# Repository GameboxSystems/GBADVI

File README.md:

# GBADVI

GBADVI is a custom DVI driver written in VHDL for the Gameboy Advance. It employs a custom PCB based around the Spartan-6 (XC6SLX9) FPGA that takes in GBA display and control signals (through SNES port), stores frames in SDRAM, and outputs a pure DVI signal through the onboard HDMI. Project includes a custom quick solder flex cable made by [Helder](https://github.com/Helder1981) (Instagram: @angryhelder) that breaks out control signals to the FPGA as well as supplies power to the GBA itself.

## Deployment

To deploy firmware to the custom PCB, the project must be built by Xilinx ISE project navigator then subsequently flashed via Xilinx Impact sofware with the Xilinx Platform Cable II. 

## To-Do/Improvements

* Design custom case
* Implement sound and audio filters
* Implement scanlines 
* Implement color filters
* Implement OSD
* Implement additional controller support
* Port to alternate FPGAs/dev boards

## Known Issues

* Power button circuitry untested in latest PCB revision. A 0ohm jumper resistor has been added as a fail safe until the circuitry is officially tested by Gamebox Systems. The repository will be updated once the circuitry is tested.

## Built With

* [Xilinx ISE](https://www.xilinx.com/products/design-tools/ise-design-suite.html) - Synthesis and deployment suite

* [Eagle](https://www.autodesk.com/products/eagle/overview?plc=F360&term=1-YEAR&support=ADVANCED&quantity=1) - PCB design software

## Contributing

GBADVI is completely open source under GPL and those wanting to contribute are welcome to do so. Please feel free to submit a pull request.

## Authors

* **Oleksandr Kiyenko** - *System Architect* - [Oleksandr Kiyenko](https://github.com/kienko)

* **Aaron Silberman** - *Hardware Engineer* - [Postman](https://github.com/GameboxSystems/)

## License

This project is licensed under the GPLv3 License - see the LICENSE.md file for details

## Acknowledgments

* **zwenergy** - Original inspiration for the project, his [gbaHD](https://github.com/zwenergy/gbaHD) is a wonderful implementation that they were kind enough to give to us all. Thank you zwenergy!
* **Helder** - Maker of the flex and all around great modder. Visit his site at https://www.heldergametech.com/ for awesome modding products!

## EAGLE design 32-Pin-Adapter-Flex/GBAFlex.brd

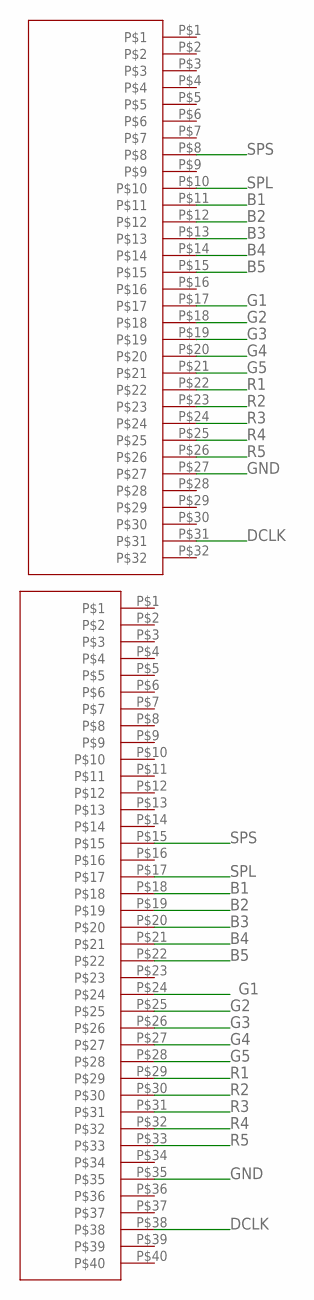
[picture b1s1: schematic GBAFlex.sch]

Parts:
U$1: 32PIN_0.5MM
U$2: 40PIN_0.5MM

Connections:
B1: U$1.P$11, U$2.P$18
B2: U$1.P$12, U$2.P$19
B3: U$1.P$13, U$2.P$20
B4: U$1.P$14, U$2.P$21
B5: U$1.P$15, U$2.P$22
DCLK: U$1.P$31, U$2.P$38
G1: U$1.P$17, U$2.P$24
G2: U$1.P$18, U$2.P$25
G3: U$1.P$19, U$2.P$26
G4: U$1.P$20, U$2.P$27
G5: U$1.P$21, U$2.P$28
GND: U$1.P$27, U$2.P$35
R1: U$1.P$22, U$2.P$29
R2: U$1.P$23, U$2.P$30
R3: U$1.P$24, U$2.P$31
R4: U$1.P$25, U$2.P$32
R5: U$1.P$26, U$2.P$33
SPL: U$1.P$10, U$2.P$17
SPS: U$1.P$8, U$2.P$15

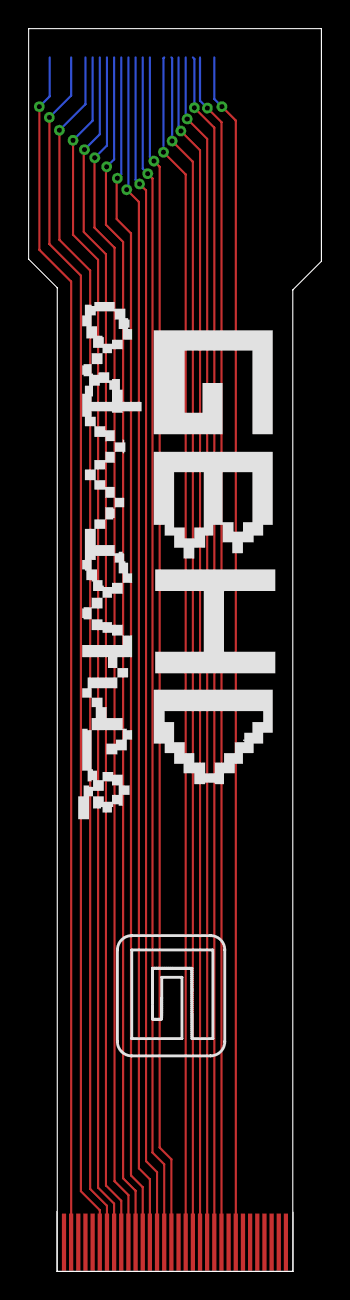
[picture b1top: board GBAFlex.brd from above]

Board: 2 copper layers, 20.4 x 86.8 mm, 4 parts (1 on the bottom side), 19 nets.

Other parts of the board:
U$3: GAMEBOXCARTBOY
U$4: GBHDADV#PNG

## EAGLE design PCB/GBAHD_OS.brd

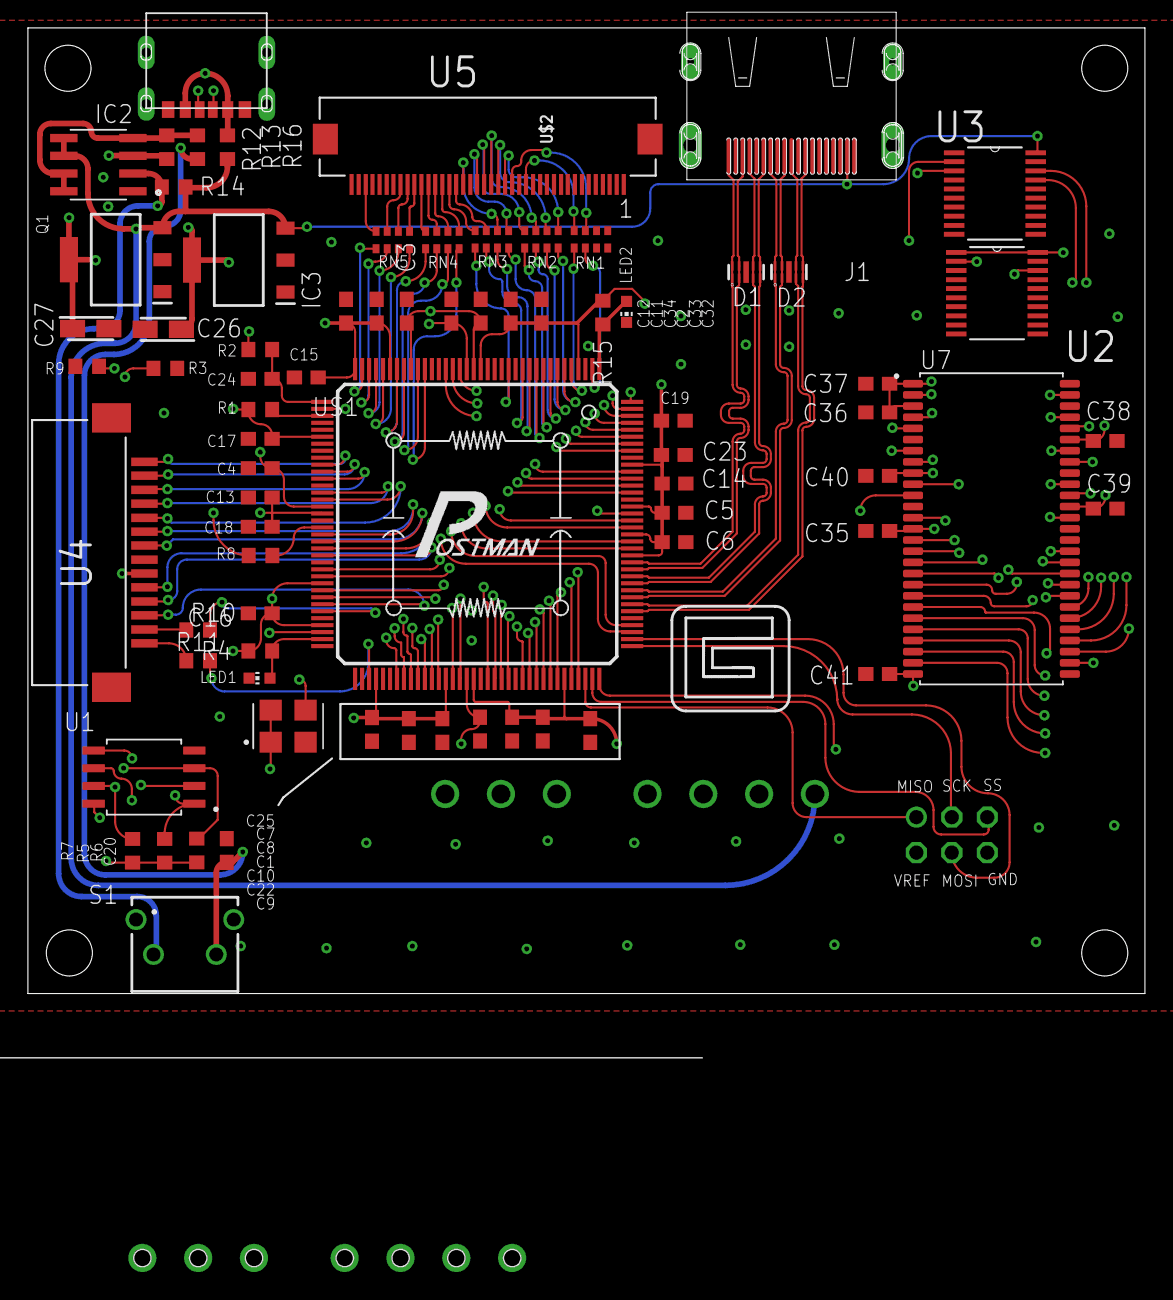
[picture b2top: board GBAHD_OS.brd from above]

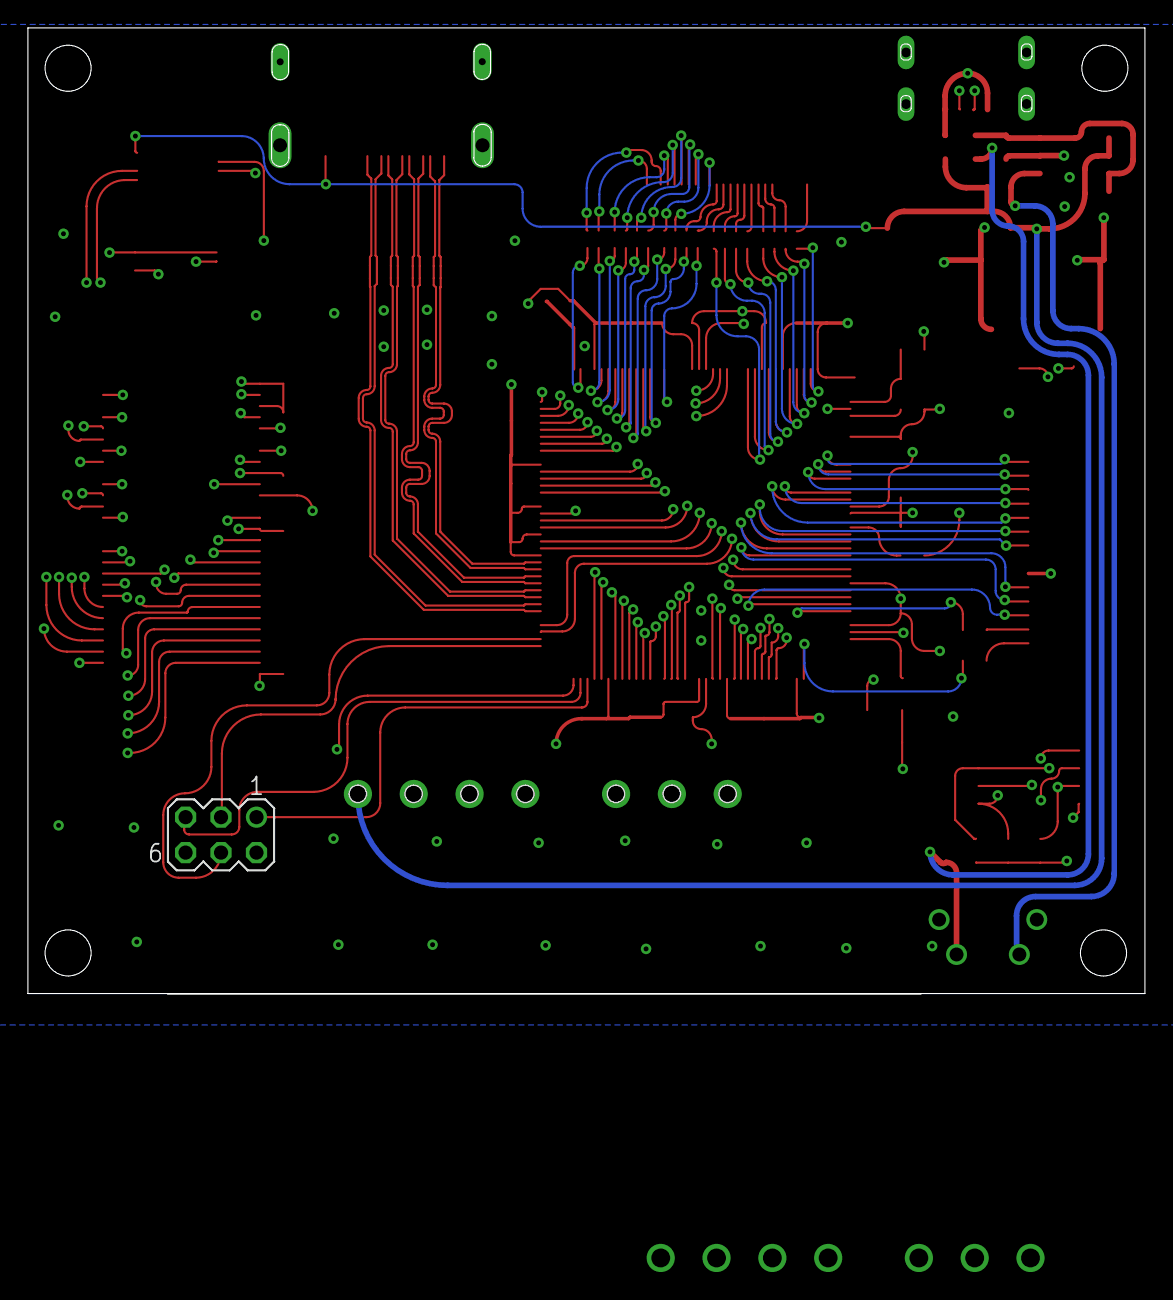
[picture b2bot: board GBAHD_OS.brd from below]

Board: 4 copper layers, 80.0 x 69.2 mm, 84 parts (2 on the bottom side), 129 nets.

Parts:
C1, C2, C3, C7, C10, C11, C12, C13, C14, C15, C16, C19, C23, C32: 4.7u; C0603
C4, C6, C9, C18, C22, C34: 0.47u; C0603
C5, C8, C17, C33: 0.47U; C0603
C20, C35, C36, C37, C38, C39, C40, C41: 1uF; C0603
C24, C25: 0.1u; C0603
C26, C27: 22uF; CAPPM3216X180N
D1, D2: RCLAMP0524PQTCT; RCLAMP0524P
IC2: AMS1117-3.3V; SOT229P700X180-4N
IC3: AMS1117-1.2V; SOT229P700X180-4N
J1: 47151-1081HDMI-001; HDMI-001
LED1, LED2: CHIP-LED0603
PROG2: MA03-2
Q1: IRF7319TR; SOIC127P600X175-8N
R1, R2, R5, R6, R7, R12, R14: 10k; R0603
R3, R9: 5.1k; R0603
R4: 2k; R0603
R8: 22R; R0603
R10, R11, R16: 0R; R0603
R13: 100k; R0603
R15: 680R; R0603
RN1, RN2, RN3, RN4, RN5: 0603-ARV
S1: 431256038726; 4312560387X6
U1: W25Q64JVSSIQ; SOIC127P790X216-8N
U2, U3: SN74LVC245APWR; SOP65P640X120-20N
U4: 52271-1469; MOLEX_52271-1469
U5: FH12A-40S-0.5SH(55); HIROSE_FH12A-40S-0.5SH(55)
U7: MT48LC16M16A2TG-6A_IT:GTR; SOP80P1176X120-54N
U$1: O50327425MEDH4MI; OSC_ECS-3518-640-B-TR
U$2: XC6SLX9-2TQG144C; TQ144
U$3, U$10: SNES_CONT
U$4: LOGO#JPG
U$5: POWER_USBC; USB-C
U$7: GAMEBOXCARTBOY
U$9, U$13, U$14, U$15: STAND-OFF

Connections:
1V2: C1.1, C2.1, C3.1, C4.1, C26.1, IC3.4, U$2.P19, U$2.P28, U$2.P52, U$2.P89, U$2.P128
3V3: C5.1, C6.1, C7.1, C8.1, C9.1, C10.1, C11.1, C12.1, C13.1, C14.1, C15.1, C16.1, C17.1, C18.1, C19.1, C22.1, C23.1, C25.1, C27.1, C32.1, C33.1, C34.1, C35.1, C36.1, C37.1, C38.1, C39.1, C40.1, C41.1, IC2.4, PROG2.2, R1.1, R2.1, R4.2, R5.2, R6.1, R7.1, R15.1, U1.8, U2.1, U2.20, U4.9, U7.1, U7.3, U7.9, U7.14, U7.27, U7.43, U7.49, U$1.1, U$1.4, U$2.P4, U$2.P18, U$2.P20, U$2.P31, U$2.P36, U$2.P42, U$2.P53, U$2.P63, U$2.P69, U$2.P76, U$2.P86, U$2.P90, U$2.P103, U$2.P122, U$2.P125, U$2.P129, U$2.P135
5V: IC2.3, IC3.3, J1.P$18, Q1.5, Q1.6, R14.2, R16.1, U3.20, U$3.5V
5V_IN: Q1.3, R12.2, R16.2, U$5.VCC, U$5.VCC1
A0: U7.23, U$2.P87
A1: U7.24, U$2.P84
A2: U7.25, U$2.P82
A3: U7.26, U$2.P80
A4: U7.29, U$2.P79
A5: U7.30, U$2.P81
A6: U7.31, U$2.P83
A7: U7.32, U$2.P85
A8: U7.33, U$2.P88
A9: U7.34, U$2.P93
A10: U7.22, U$2.P92
A11: U7.35, U$2.P95
A12: U7.36, U$2.P98
A_BUTTON: U4.11, U$2.P59
B1: RN2.4, U$2.P6
B1_GBA: RN2.5, U5.18
B2: RN2.3, U$2.P7
B2_GBA: RN2.6, U5.19
B3: RN2.2, U$2.P8
B3_GBA: RN2.7, U5.20
B4: RN2.1, U$2.P9
B4_GBA: RN2.8, U5.21
B5: RN3.4, U$2.P10
B5_GBA: RN3.5, U5.22
BA0: U7.20, U$2.P97
BA1: U7.21, U$2.P94
B_BUTTON: U4.12, U$2.P66
CAS: U7.17, U$2.P104
CCLK: U1.6, U$2.P70
CKE_RAM: U7.37, U$2.P100
CLK_NES: U3.2, U$3.CLOCK
CLK_NES_FPGA: U3.18, U$2.P23
CLK_RAM: U7.38, U$2.P102
CS: U7.19, U$2.P99
DATA_NES: U2.2, U$3.DATA
DATA_NES_FPGA: U2.18, U$2.P21
DCLK: RN5.1, U$2.P35
DCLK_GBA: RN5.8, U5.38
DOWN_BUTTON: U4.4, U$2.P50
DQ0: U7.2, U$2.P144
DQ1: U7.4, U$2.P142
DQ2: U7.5, U$2.P140
DQ3: U7.7, U$2.P138
DQ4: U7.8, U$2.P134
DQ5: U7.10, U$2.P132
DQ6: U7.11, U$2.P127
DQ7: U7.13, U$2.P124
DQ8: U7.42, U$2.P123
DQ9: U7.44, U$2.P126
DQ10: U7.45, U$2.P131
DQ11: U7.47, U$2.P133
DQ12: U7.48, U$2.P137
DQ13: U7.50, U$2.P139
DQ14: U7.51, U$2.P141
DQ15: U7.53, U$2.P143
DQMH: U7.39, U$2.P105
DQML: U7.15, U$2.P112
FLASH_CS: R5.1, U1.1, U$2.P38
FLASH_D0: U1.5, U$2.P64
FLASH_D1: U1.2, U$2.P65
FLASH_D2: R6.2, U1.3, U$2.P62
FLASH_D3: R7.2, U1.7, U$2.P61
G1: RN3.3, U$2.P11
G1_GBA: RN3.6, U5.24
G2: RN3.2, U$2.P12
G2_GBA: RN3.7, U5.25
G3: RN3.1, U$2.P14
G3_GBA: RN3.8, U5.26
G4: RN4.4, U$2.P26
G4_GBA: RN4.5, U5.27
G5: RN4.3, U$2.P27
G5_GBA: RN4.6, U5.28
GND: C1.2, C2.2, C3.2, C4.2, C5.2, C6.2, C7.2, C8.2, C9.2, C10.2, C11.2, C12.2, C13.2, C14.2, C15.2, C16.2, C17.2, C18.2, C19.2, C20.2, C22.2, C23.2, C24.2, C25.2, C26.2, C27.2, C32.2, C33.2, C34.2, C35.2, C36.2, C37.2, C38.2, C39.2, C40.2, C41.2, D1.3, D1.8, D2.3, D2.8, IC2.1, IC3.1, J1.P$2, J1.P$5, J1.P$8, J1.P$11, LED1.C, LED2.C, PROG2.6, Q1.1, R3.2, R9.2, S1.1, S1.4, U1.4, U2.10, U2.11, U2.12, U2.13, U2.14, U2.15, U2.16, U2.17, U2.19, U3.1, U3.10, U3.11, U3.12, U3.13, U3.14, U3.15, U3.19, U4.8, U5.35, U7.6, U7.12, U7.28, U7.41, U7.46, U7.52, U7.54, U$1.2, U$2.P3, U$2.P13, U$2.P25, U$2.P49, U$2.P54, U$2.P60, U$2.P68, U$2.P73, U$2.P77, U$2.P91, U$2.P96, U$2.P108, U$2.P113, U$2.P130, U$2.P136, U$3.GND, U$5.GND, U$5.GND1, U$5.P$7, U$5.P$8, U$5.P$9, U$5.P$10
LATCH_NES: U3.3, U$3.LATCH
LATCH_NES_FPGA: U3.17, U$2.P22
LEFT_BUTTON: U4.3, U$2.P48
L_BUTTON: U4.1, U$2.P46
MISO/TDO: PROG2.1, U$2.P106
MOSI/TDI: PROG2.4, U$2.P110
unnamed: R1.2, U$2.P39
unnamed: C24.1, R2.2, U$2.P37
unnamed: R3.1, U$5.CC1
unnamed: R8.1, U$1.3
unnamed: R9.1, U$5.CC2
unnamed: R10.2, U$2.P67
unnamed: R11.2, U$2.P75
unnamed: Q1.2, R14.1, S1.2
unnamed: Q1.4, Q1.7, Q1.8, R12.1, R13.2
unnamed: C20.1, R13.1, S1.3
unnamed: LED1.A, R4.1, U$2.P71
unnamed: LED2.A, R15.2, U$2.P1
OSC_OUT: R8.2, U$2.P55
R1: RN4.2, U$2.P29
R1_GBA: RN4.7, U5.29
R2: RN4.1, U$2.P30
R2_GBA: RN4.8, U5.30
R3: RN5.4, U$2.P32
R3_GBA: RN5.5, U5.31
R4: RN5.3, U$2.P33
R4_GBA: RN5.6, U5.32
R5: RN5.2, U$2.P34
R5_GBA: RN5.7, U5.33
RAS: U7.18, U$2.P101
RIGHT_BUTTON: U4.5, U$2.P51
R_BUTTON: U4.10, U$2.P58
SCK/TCK: PROG2.3, U$2.P109
SELECT_BUTTON: U4.6, U$2.P56
SO1: R10.1, U4.13
SO2: R11.1, U4.14
SPL: RN1.6, U$2.P2
SPL_GBA: RN1.3, U5.17
SPS: RN1.5, U$2.P5
SPS_GBA: RN1.4, U5.15
SS/TMS: PROG2.5, U$2.P107
START_BUTTON: U4.7, U$2.P57
TMDSCLK_N: D2.5, D2.6, J1.P$12, U$2.P114
TMDSCLK_P: D2.4, D2.7, J1.P$10, U$2.P115
TMDSD0_N: D2.2, D2.9, J1.P$9, U$2.P116
TMDSD0_P: D2.1, D2.10, J1.P$7, U$2.P117
TMDSD1_N: D1.5, D1.6, J1.P$6, U$2.P118
TMDSD1_P: D1.4, D1.7, J1.P$4, U$2.P119
TMDSD2_N: D1.2, D1.9, J1.P$3, U$2.P120
TMDSD2_P: D1.1, D1.10, J1.P$1, U$2.P121
UP_BUTTON: U4.2, U$2.P47
WE: U7.16, U$2.P111

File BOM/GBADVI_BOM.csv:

Qty,Value,LCSC Part Num,Package,Parts,Notes
14,4.7u,*,C0603,"C1, C2, C3, C7, C10, C11, C12, C13, C14, C15, C16, C19, C23, C32",
8,1uF,*,C0603,"C20, C35, C36, C37, C38, C39, C40, C41",
2,0.1u,*,C0603,"C24, C25",
2,22uF,*,CAPPM3216X180N,"C26, C27",
6,0.47u,*,C0603,"C4, C6, C9, C18, C22, C34",
4,0.47U,*,C0603,"C5, C8, C17, C33",
2,RCLAMP0524PQTCT,C316044,RCLAMP0524P,"D1, D2",
1,AMS1117-3.3V,C351784,SOT229P700X180-4N,IC2,
1,AMS1117-1.2V,C347218,SOT229P700X180-4N,IC3,
1,47151-1081HDMI-001,C138388,HDMI-001,J1,
2,,*,CHIP-LED0603,"LED1, LED2",
1,IRF7319TR,C693304,SOIC127P600X175-8N,Q1,
7,10k,*,R0603,"R1, R2, R5, R6, R7, R12, R14",
3,0R,*,R0603,"R10, R11, R16",DNI
1,100k,*,R0603,R13,
1,680R,*,R0603,R15,
2,5.1k,*,R0603,"R3, R9",
1,2k,*,R0603,R4,
1,22R,*,R0603,R8,
5,10R,*,0603-ARV,"RN1, RN2, RN3, RN4, RN5",
1,4.31256E+11,C231668,4312560387X6,S1,
1,O50327425MEDH4MI,C79434,OSC_ECS-3518-640-B-TR,U$1,
1,XC6SLX9-2TQG144C,C27408,TQ144,U$2,
1,SNES_CONT,*,SNES_CONT,U$3,"https://www.aliexpress.com/item/32828768824.html?spm=a2g0o.p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,searchweb201602_,searchweb201603_"
1,POWER_USBC,C283540,USB-C,U$5,
1,W25Q64JVSSIQ,C83140,SOIC127P790X216-8N,U1,
2,SN74LVC245APWR,C7848,SOP65P640X120-20N,"U2, U3",
1,52271-1469,*,MOLEX_52271-1469,U4,
1,FH12A-40S-0.5SH(55),C262686,HIROSE_FH12A-40S-0.5SH(55),U5,
1,MT48LC16M16A2TG-6A_IT:GTR,C41881,SOP80P1176X120-54N,U7,
1,40pin 0.5mm FFC cable,*,*,*,

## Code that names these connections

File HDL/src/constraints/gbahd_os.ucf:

# Clock
NET "pclk_in" LOC = P55	| IOSTANDARD = LVCMOS33;
NET "pclk_in" TNM_NET = pclk_in;
TIMESPEC TS_pclk_in = PERIOD "pclk_in" 74.25 MHz HIGH 50%;

# SDRAM
NET "sdram_clk"  	LOC = P102 | IOSTANDARD = LVTTL | SLEW = FAST;
NET "sdram_cle"  	LOC = P100 | IOSTANDARD = LVTTL | SLEW = FAST;
#NET "sdram_dqm<1>" LOC = P112 | IOSTANDARD = LVTTL | SLEW = FAST;
NET "sdram_dqm"		LOC = P105 | IOSTANDARD = LVTTL | SLEW = FAST;
NET "sdram_cs"   	LOC = P99  | IOSTANDARD = LVTTL | SLEW = FAST;
NET "sdram_we"   	LOC = P111 | IOSTANDARD = LVTTL | SLEW = FAST;
NET "sdram_cas"  	LOC = P104 | IOSTANDARD = LVTTL | SLEW = FAST;
NET "sdram_ras"  	LOC = P101 | IOSTANDARD = LVTTL | SLEW = FAST;
NET "sdram_ba<0>"	LOC = P97  | IOSTANDARD = LVTTL | SLEW = FAST;
NET "sdram_ba<1>"	LOC = P94  | IOSTANDARD = LVTTL | SLEW = FAST;
NET "sdram_a<0>" 	LOC = P87  | IOSTANDARD = LVTTL | SLEW = FAST;
NET "sdram_a<1>" 	LOC = P84  | IOSTANDARD = LVTTL | SLEW = FAST;
NET "sdram_a<2>" 	LOC = P82  | IOSTANDARD = LVTTL | SLEW = FAST;
NET "sdram_a<3>" 	LOC = P80  | IOSTANDARD = LVTTL | SLEW = FAST;
NET "sdram_a<4>" 	LOC = P79  | IOSTANDARD = LVTTL | SLEW = FAST;
NET "sdram_a<5>" 	LOC = P81  | IOSTANDARD = LVTTL | SLEW = FAST;
NET "sdram_a<6>" 	LOC = P83  | IOSTANDARD = LVTTL | SLEW = FAST;
NET "sdram_a<7>" 	LOC = P85  | IOSTANDARD = LVTTL | SLEW = FAST;
NET "sdram_a<8>" 	LOC = P88  | IOSTANDARD = LVTTL | SLEW = FAST;
NET "sdram_a<9>" 	LOC = P93  | IOSTANDARD = LVTTL | SLEW = FAST;
NET "sdram_a<10>"	LOC = P92  | IOSTANDARD = LVTTL | SLEW = FAST;
NET "sdram_a<11>"	LOC = P95  | IOSTANDARD = LVTTL | SLEW = FAST;
NET "sdram_a<12>"	LOC = P98  | IOSTANDARD = LVTTL | SLEW = FAST;
NET "sdram_dq<0>"	LOC = P144 | IOSTANDARD = LVTTL | SLEW = FAST;
#NET "sdram_dq<1>"	LOC = P142 | IOSTANDARD = LVTTL | SLEW = FAST;
NET "sdram_dq<1>"	LOC = P140 | IOSTANDARD = LVTTL | SLEW = FAST;
NET "sdram_dq<3>"	LOC = P138 | IOSTANDARD = LVTTL | SLEW = FAST;
NET "sdram_dq<2>"	LOC = P134 | IOSTANDARD = LVTTL | SLEW = FAST;
#NET "sdram_dq<5>"	LOC = P132 | IOSTANDARD = LVTTL | SLEW = FAST;
NET "sdram_dq<3>"	LOC = P127 | IOSTANDARD = LVTTL | SLEW = FAST;
#NET "sdram_dq<7>"	LOC = P124 | IOSTANDARD = LVTTL | SLEW = FAST;
#NET "sdram_dq<8>"	LOC = P123 | IOSTANDARD = LVTTL | SLEW = FAST;
NET "sdram_dq<4>"	LOC = P126 | IOSTANDARD = LVTTL | SLEW = FAST;
#NET "sdram_dq<10>"	LOC = P131 | IOSTANDARD = LVTTL | SLEW = FAST;
NET "sdram_dq<5>"	LOC = P133 | IOSTANDARD = LVTTL | SLEW = FAST;
#NET "sdram_dq<12>"	LOC = P137 | IOSTANDARD = LVTTL | SLEW = FAST;
NET "sdram_dq<6>"	LOC = P139 | IOSTANDARD = LVTTL | SLEW = FAST;
#NET "sdram_dq<14>"	LOC = P141 | IOSTANDARD = LVTTL | SLEW = FAST;
NET "sdram_dq<7>"	LOC = P143 | IOSTANDARD = LVTTL | SLEW = FAST;

## SDRAM
#NET "sdram_clk"  	LOC = P102 | IOSTANDARD = LVTTL | SLEW = FAST;
#NET "sdram_cle"  	LOC = P100 | IOSTANDARD = LVTTL | SLEW = FAST;
#NET "sdram_dqm<0>"	LOC = P112 | IOSTANDARD = LVTTL | SLEW = FAST;
#NET "sdram_dqm<1>"	LOC = P105 | IOSTANDARD = LVTTL | SLEW = FAST;
#NET "sdram_cs"   	LOC = P99  | IOSTANDARD = LVTTL | SLEW = FAST;
#NET "sdram_we"   	LOC = P111 | IOSTANDARD = LVTTL | SLEW = FAST;
#NET "sdram_cas"  	LOC = P104 | IOSTANDARD = LVTTL | SLEW = FAST;
#NET "sdram_ras"  	LOC = P101 | IOSTANDARD = LVTTL | SLEW = FAST;
#NET "sdram_ba<0>"	LOC = P97  | IOSTANDARD = LVTTL | SLEW = FAST;
#NET "sdram_ba<1>"	LOC = P94  | IOSTANDARD = LVTTL | SLEW = FAST;
#NET "sdram_a<0>" 	LOC = P87  | IOSTANDARD = LVTTL | SLEW = FAST;
#NET "sdram_a<1>" 	LOC = P84  | IOSTANDARD = LVTTL | SLEW = FAST;
#NET "sdram_a<2>" 	LOC = P82  | IOSTANDARD = LVTTL | SLEW = FAST;
#NET "sdram_a<3>" 	LOC = P80  | IOSTANDARD = LVTTL | SLEW = FAST;
#NET "sdram_a<4>" 	LOC = P79  | IOSTANDARD = LVTTL | SLEW = FAST;
#NET "sdram_a<5>" 	LOC = P81  | IOSTANDARD = LVTTL | SLEW = FAST;
#NET "sdram_a<6>" 	LOC = P83  | IOSTANDARD = LVTTL | SLEW = FAST;
#NET "sdram_a<7>" 	LOC = P85  | IOSTANDARD = LVTTL | SLEW = FAST;
#NET "sdram_a<8>" 	LOC = P88  | IOSTANDARD = LVTTL | SLEW = FAST;
#NET "sdram_a<9>" 	LOC = P93  | IOSTANDARD = LVTTL | SLEW = FAST;
#NET "sdram_a<10>"	LOC = P92  | IOSTANDARD = LVTTL | SLEW = FAST;
#NET "sdram_a<11>"	LOC = P95  | IOSTANDARD = LVTTL | SLEW = FAST;
#NET "sdram_a<12>"	LOC = P98  | IOSTANDARD = LVTTL | SLEW = FAST;
#NET "sdram_dq<0>"	LOC = P144 | IOSTANDARD = LVTTL | SLEW = FAST;
#NET "sdram_dq<1>"	LOC = P142 | IOSTANDARD = LVTTL | SLEW = FAST;
#NET "sdram_dq<2>"	LOC = P140 | IOSTANDARD = LVTTL | SLEW = FAST;
#NET "sdram_dq<3>"	LOC = P138 | IOSTANDARD = LVTTL | SLEW = FAST;
#NET "sdram_dq<4>"	LOC = P134 | IOSTANDARD = LVTTL | SLEW = FAST;
#NET "sdram_dq<5>"	LOC = P132 | IOSTANDARD = LVTTL | SLEW = FAST;
#NET "sdram_dq<6>"	LOC = P127 | IOSTANDARD = LVTTL | SLEW = FAST;
#NET "sdram_dq<7>"	LOC = P124 | IOSTANDARD = LVTTL | SLEW = FAST;
##NET "sdram_dq<8>"	LOC = P123 | IOSTANDARD = LVTTL | SLEW = FAST;
##NET "sdram_dq<9>"	LOC = P126 | IOSTANDARD = LVTTL | SLEW = FAST;
##NET "sdram_dq<10>"	LOC = P131 | IOSTANDARD = LVTTL | SLEW = FAST;
##NET "sdram_dq<11>"	LOC = P133 | IOSTANDARD = LVTTL | SLEW = FAST;
##NET "sdram_dq<12>"	LOC = P137 | IOSTANDARD = LVTTL | SLEW = FAST;
##NET "sdram_dq<13>"	LOC = P139 | IOSTANDARD = LVTTL | SLEW = FAST;
##NET "sdram_dq<14>"	LOC = P141 | IOSTANDARD = LVTTL | SLEW = FAST;
##NET "sdram_dq<15>"	LOC = P143 | IOSTANDARD = LVTTL | SLEW = FAST;



#NET "led" 			LOC = P1   | IOSTANDARD = LVCMOS33;

# HDMI1
NET "hdmi1_d_p<2>"	LOC = P121 | IOSTANDARD = TMDS_33;
NET "hdmi1_d_n<2>"	LOC = P120 | IOSTANDARD = TMDS_33;
NET "hdmi1_d_p<1>"	LOC = P119 | IOSTANDARD = TMDS_33;
NET "hdmi1_d_n<1>"	LOC = P118 | IOSTANDARD = TMDS_33;
NET "hdmi1_d_p<0>"	LOC = P117 | IOSTANDARD = TMDS_33;
NET "hdmi1_d_n<0>"	LOC = P116 | IOSTANDARD = TMDS_33;
NET "hdmi1_c_p"   	LOC = P115 | IOSTANDARD = TMDS_33;
NET "hdmi1_c_n"	  	LOC = P114 | IOSTANDARD = TMDS_33;


NET "gba_clk"  LOC = P35	| IOSTANDARD = LVCMOS33;
NET "gba_hs"   LOC = P1		| IOSTANDARD = LVCMOS33;	# LP
NET "gba_vs"   LOC = P5 	| IOSTANDARD = LVCMOS33;	# SPS
NET "gba_r<0>" LOC = P29	| IOSTANDARD = LVCMOS33;
NET "gba_r<1>" LOC = P30	| IOSTANDARD = LVCMOS33;
NET "gba_r<2>" LOC = P32	| IOSTANDARD = LVCMOS33;
NET "gba_r<3>" LOC = P33	| IOSTANDARD = LVCMOS33;
NET "gba_r<4>" LOC = P34	| IOSTANDARD = LVCMOS33;
NET "gba_g<0>" LOC = P11	| IOSTANDARD = LVCMOS33;
NET "gba_g<1>" LOC = P12	| IOSTANDARD = LVCMOS33;
NET "gba_g<2>" LOC = P14	| IOSTANDARD = LVCMOS33;
NET "gba_g<3>" LOC = P26	| IOSTANDARD = LVCMOS33;
NET "gba_g<4>" LOC = P27	| IOSTANDARD = LVCMOS33;
NET "gba_b<0>" LOC = P6		| IOSTANDARD = LVCMOS33;
NET "gba_b<1>" LOC = P7		| IOSTANDARD = LVCMOS33;
NET "gba_b<2>" LOC = P8		| IOSTANDARD = LVCMOS33;
NET "gba_b<3>" LOC = P9		| IOSTANDARD = LVCMOS33;
NET "gba_b<4>" LOC = P10	| IOSTANDARD = LVCMOS33;

# Controllers
NET "DATA_NES"		LOC = P21		| IOSTANDARD = LVCMOS33;
NET "CLK_NES"		LOC = P23		| IOSTANDARD = LVCMOS33;
NET "LATCH_NES"		LOC = P22		| IOSTANDARD = LVCMOS33;
NET "L_BUTTON"		LOC = P46		| IOSTANDARD = LVCMOS33;
NET "UP_BUTTON"		LOC = P47		| IOSTANDARD = LVCMOS33;
NET "LEFT_BUTTON"	LOC = P48		| IOSTANDARD = LVCMOS33;
NET "DOWN_BUTTON"	LOC = P50		| IOSTANDARD = LVCMOS33;
NET "RIGHT_BUTTON"  LOC = P51		| IOSTANDARD = LVCMOS33;
NET "SELECT_BUTTON"	LOC = P56		| IOSTANDARD = LVCMOS33;
NET "START_BUTTON"  LOC = P57		| IOSTANDARD = LVCMOS33;
NET "R_BUTTON"		LOC = P58		| IOSTANDARD = LVCMOS33;
NET "A_BUTTON"		LOC = P59		| IOSTANDARD = LVCMOS33;
NET "B_BUTTON"		LOC = P66		| IOSTANDARD = LVCMOS33;

# Audio
#NET "SO1"			LOC = P67		| IOSTANDARD = LVCMOS33;
#NET "SO2"			LOC = P74		| IOSTANDARD = LVCMOS33;

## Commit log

2021-05-02 first commit GBADVI v1.0
2021-05-02 add readme and flex cable
2021-05-02 update PCB file names
2021-05-02 Updated Folder Title
2021-05-09 Updated .brd source
2022-08-15 Added 32 pin flex cable adapter files
2022-10-10 Added test pad quick solder flex gerber files
2023-03-07 Updated board for i2c EEPROM and added WS2812B LEDs

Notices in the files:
parts and their libraries:
SparkFun-Electromechanical: Licensing: CC v3.0 Share-Alike You are welcome to use this library for commercial purposes.
